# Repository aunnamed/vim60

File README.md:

## Vim60 Mechanical Keyboard

> Description
>
> * A 60% layout mechanical keyboard.
>
>

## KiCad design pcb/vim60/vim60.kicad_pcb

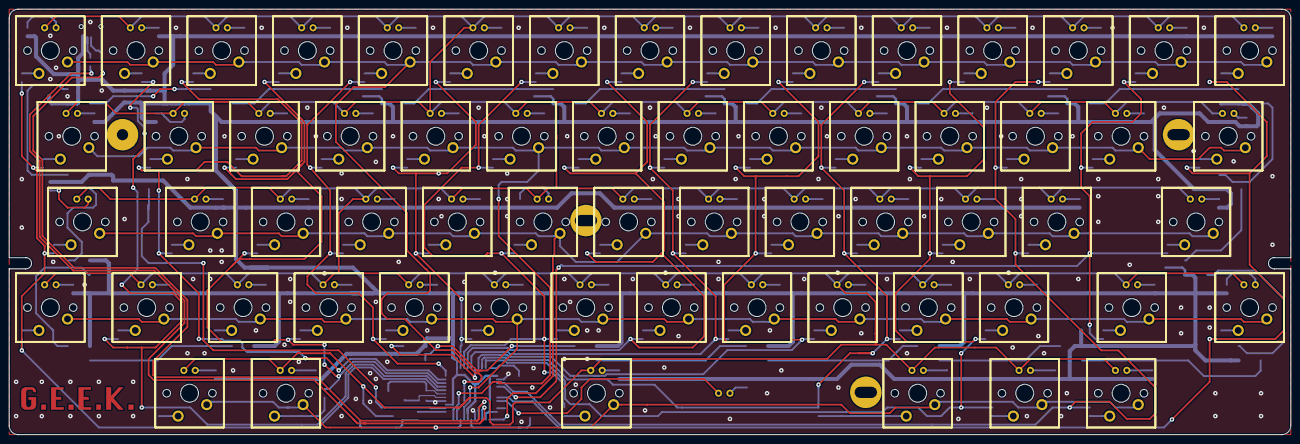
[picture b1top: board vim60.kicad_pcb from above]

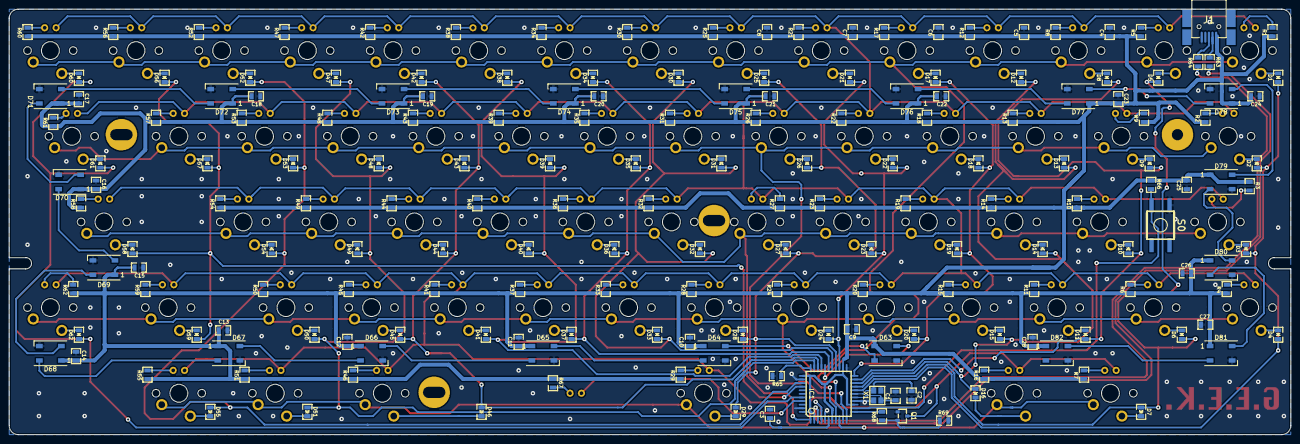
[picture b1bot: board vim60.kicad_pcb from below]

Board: 2 copper layers, 285.0 x 94.6 mm, 313 parts (184 on the bottom side), 180 nets.

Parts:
C1, C2: 22p; 0805C
C3, C4: 1u; 0805C
C5, C6, C7, C8: 100n; 0805C
C9, C10, C11, C12, C13, C14, C15, C16, C17, C18, C19, C20, C21, C22, C23, C24, C25, C26, C27, C28: 100nf; 0805C
D1, D2, D3, D4, D5, D6, D7, D8, D9, D10, D11, D12, D13, D14, D15, D16, D17, D18, D19, D20, D21, D22, D23, D24, D25, D26, D27, D28, D29, D30, D31, D32, D33, D34, D35, D36, D37, D38, D39, D40, D41, D42, D43, D44, D45, D46, D47, D48, D49, D50, D51, D52, D53, D54, D55, D56, D57, D58, D59, D60, D61, D62: 1N4148; 0805D
D63, D64, D65, D66, D67, D68, D69, D70, D71, D72, D73, D74, D75, D76, D77, D78, D79, D80, D81, D82: WS2812B; LED_WS2812B_PLCC4_5.0x5.0mm_P3.2mm
DB1, DB2, DB3, DB4, DB5, DB6, DB7, DB8, DB9, DB10, DB11, DB12, DB13, DB14, DB15, DB16, DB17, DB18, DB19, DB20, DB21, DB22, DB23, DB24, DB25, DB26, DB27, DB28, DB29, DB30, DB31, DB32, DB33, DB34, DB35, DB36, DB37, DB38, DB39, DB40, DB41, DB42, DB43, DB44, DB45, DB46, DB47, DB48, DB49, DB50, DB51, DB52, DB53, DB54, DB55, DB56, DB57, DB58, DB59, DB60, DB61, DB62: LED; MX1A-led
DB63: LED; caps_led
HOLE: VAL**; PKRH
HOLE#2, HOLE#3: VAL**; PKRH
HOLE#4: VAL**; PKRHC
IC1: ATMEGA32U4; TQFP44
J1: USBMINI_B05; 67503
Q1: NPN; 2SC5866
R1, R2, R3, R4, R5, R6, R7, R8, R9, R10, R11, R12, R13, R14, R15, R16, R17, R18, R19, R20, R21, R22, R23, R24, R25, R26, R27, R28, R29, R30, R31, R32, R33, R34, R35, R36, R37, R38, R39, R40, R41, R42, R43, R44, R45, R46, R47, R48, R49, R50, R51, R52, R53, R54, R55, R56, R57, R58, R59, R60, R61, R62: 250; 0805R
R63, R64: 22; 0805R
R65, R66: 10k; 0805R
R67: 300; 0805R
R68, R69: R; 0805R
S0: DTSM-6; KSEM31GLFS
S1, S2, S3, S4, S5, S6, S7, S8, S9, S10, S11, S12, S13, S14, S15, S16, S17, S18, S19, S20, S21, S22, S23, S24, S25, S26, S27, S28, S29, S30, S31, S32, S33, S34, S35, S36, S37, S38, S39, S40, S41, S42, S43, S44, S45, S46, S47, S48, S49, S50, S51, S52, S53, S54, S55, S56, S57, S58, S59, S60, S61, S62: MX1A
X1: ASX4; 4-SMD

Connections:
/CAPS_LED: DB63.2, IC1.41
/bl: IC1.12, R68.2
/col01: D1.1, D2.1, D3.1, D4.1, IC1.18
/col02: D5.1, D6.1, D7.1, IC1.19
/col03: D8.1, D9.1, D10.1, D11.1, IC1.21
/col04: D12.1, D13.1, D14.1, D15.1, D16.1, IC1.20
/col05: D17.1, D18.1, D19.1, D20.1, IC1.22
/col06: D21.1, D22.1, D23.1, D24.1, IC1.25
/col07: D25.1, D26.1, D27.1, D28.1, D29.1, IC1.26
/col08: D30.1, D31.1, D32.1, D33.1, IC1.27
/col09: D34.1, D35.1, D36.1, D37.1, IC1.28
/col10: D38.1, D39.1, D40.1, D41.1, IC1.30
/col11: D42.1, D43.1, D44.1, D45.1, D46.1, IC1.31
/col12: D47.1, D48.1, D49.1, D50.1, D51.1, IC1.32
/col13: D52.1, D53.1, D54.1, D55.1, IC1.36
/col14: D56.1, D57.1, D58.1, D59.1, IC1.37
/col15: D60.1, D61.1, D62.1, IC1.40
/rgb: D63.4, IC1.29
/row01: IC1.10, S1.1, S5.1, S8.1, S12.1, S17.1, S21.1, S25.1, S30.1, S34.1, S38.1, S42.1, S47.1, S52.1, S56.1, S60.1
/row02: IC1.11, S2.1, S9.1, S13.1, S18.1, S22.1, S26.1, S31.1, S35.1, S39.1, S43.1, S48.1, S53.1, S57.1, S61.1
/row03: IC1.1, S3.1, S10.1, S14.1, S19.1, S23.1, S27.1, S32.1, S36.1, S40.1, S44.1, S49.1, S54.1, S58.1
/row04: IC1.8, S4.1, S6.1, S11.1, S15.1, S20.1, S24.1, S28.1, S33.1, S37.1, S41.1, S45.1, S50.1, S59.1, S62.1
/row05: IC1.9, S7.1, S16.1, S29.1, S46.1, S51.1, S55.1
GND: C1.2, C2.2, C3.2, C4.2, C5.2, C6.2, C7.2, C8.2, C9.1, C10.1, C11.1, C12.1, C13.1, C14.1, C15.1, C16.1, C17.1, C18.1, C19.1, C20.1, C21.1, C22.1, C23.1, C24.1, C25.1, C26.1, C27.1, C28.1, D63.3, D64.3, D65.3, D66.3, D67.3, D68.3, D69.3, D70.3, D71.3, D72.3, D73.3, D74.3, D75.3, D76.3, D77.3, D78.3, D79.3, D80.3, D81.3, D82.3, IC1.5, IC1.15, IC1.23, IC1.35, IC1.43, J1.5, Q1.1, R65.2, R69.2, S0.1, X1.2, X1.4
unnamed: C1.1, IC1.16, X1.1
unnamed: C2.1, IC1.17, X1.3
unnamed: C3.1, IC1.6
unnamed: D1.2, S1.2
unnamed: D2.2, S2.2
unnamed: D3.2, S3.2
unnamed: D4.2, S4.2
unnamed: D5.2, S5.2
unnamed: D6.2, S6.2
unnamed: D7.2, S7.2
unnamed: D8.2, S8.2
unnamed: D9.2, S9.2
unnamed: D10.2, S10.2
unnamed: D11.2, S11.2
unnamed: D12.2, S12.2
unnamed: D13.2, S13.2
unnamed: D14.2, S14.2
unnamed: D15.2, S15.2
unnamed: D16.2, S16.2
unnamed: D17.2, S17.2
unnamed: D18.2, S18.2
unnamed: D19.2, S19.2
unnamed: D20.2, S20.2
unnamed: D21.2, S21.2
unnamed: D22.2, S22.2
unnamed: D23.2, S23.2
unnamed: D24.2, S24.2
unnamed: D25.2, S25.2
unnamed: D26.2, S26.2
unnamed: D27.2, S27.2
unnamed: D28.2, S28.2
unnamed: D29.2, S29.2
unnamed: D30.2, S30.2
unnamed: D31.2, S31.2
unnamed: D32.2, S32.2
unnamed: D33.2, S33.2
unnamed: D34.2, S34.2
unnamed: D35.2, S35.2
unnamed: D36.2, S36.2
unnamed: D37.2, S37.2
unnamed: D38.2, S38.2
unnamed: D39.2, S39.2
unnamed: D40.2, S40.2
unnamed: D41.2, S41.2
unnamed: D42.2, S42.2
unnamed: D43.2, S43.2
unnamed: D44.2, S44.2
unnamed: D45.2, S45.2
unnamed: D46.2, S46.2
unnamed: D47.2, S47.2
unnamed: D48.2, S48.2
unnamed: D49.2, S49.2
unnamed: D50.2, S50.2
unnamed: D51.2, S51.2
unnamed: D52.2, S52.2
unnamed: D53.2, S53.2
unnamed: D54.2, S54.2
unnamed: D55.2, S55.2
unnamed: D56.2, S56.2
unnamed: D57.2, S57.2
unnamed: D58.2, S58.2
unnamed: D59.2, S59.2
unnamed: D60.2, S60.2
unnamed: D61.2, S61.2
unnamed: D62.2, S62.2
unnamed: D63.2, D64.4
unnamed: D64.2, D65.4
unnamed: D65.2, D66.4
unnamed: D66.2, D67.4
unnamed: D67.2, D68.4
unnamed: D68.2, D69.4
unnamed: D69.2, D70.4
unnamed: D70.2, D71.4
unnamed: D71.2, D72.4
unnamed: D72.2, D73.4
unnamed: D73.2, D74.4
unnamed: D74.2, D75.4
unnamed: D75.2, D76.4
unnamed: D76.2, D77.4
unnamed: D77.2, D78.4
unnamed: D78.2, D79.4
unnamed: D79.2, D80.4
unnamed: D80.2, D81.4
unnamed: D81.2, D82.4
unnamed: DB1.1, R1.2
unnamed: DB1.2, DB2.2, DB3.2, DB4.2, DB5.2, DB6.2, DB7.2, DB8.2, DB9.2, DB10.2, DB11.2, DB12.2, DB13.2, DB14.2, DB15.2, DB16.2, DB17.2, DB18.2, DB19.2, DB20.2, DB21.2, DB22.2, DB23.2, DB24.2, DB25.2, DB26.2, DB27.2, DB28.2, DB29.2, DB30.2, DB31.2, DB32.2, DB33.2, DB34.2, DB35.2, DB36.2, DB37.2, DB38.2, DB39.2, DB40.2, DB41.2, DB42.2, DB43.2, DB44.2, DB45.2, DB46.2, DB47.2, DB48.2, DB49.2, DB50.2, DB51.2, DB52.2, DB53.2, DB54.2, DB55.2, DB56.2, DB57.2, DB58.2, DB59.2, DB60.2, DB61.2, DB62.2, Q1.3
unnamed: DB2.1, R2.2
unnamed: DB3.1, R3.2
unnamed: DB4.1, R4.2
unnamed: DB5.1, R5.2
unnamed: DB6.1, R6.2
unnamed: DB7.1, R7.2
unnamed: DB8.1, R8.2
unnamed: DB9.1, R9.2
unnamed: DB10.1, R10.2
unnamed: DB11.1, R11.2
unnamed: DB12.1, R12.2
unnamed: DB13.1, R13.2
unnamed: DB14.1, R14.2
unnamed: DB15.1, R15.2
unnamed: DB16.1, R16.2
unnamed: DB17.1, R17.2
unnamed: DB18.1, R18.2
unnamed: DB19.1, R19.2
unnamed: DB20.1, R20.2
unnamed: DB21.1, R21.2
unnamed: DB22.1, R22.2
unnamed: DB23.1, R23.2
unnamed: DB24.1, R24.2
unnamed: DB25.1, R25.2
unnamed: DB26.1, R26.2
unnamed: DB27.1, R27.2
unnamed: DB28.1, R28.2
unnamed: DB29.1, R29.2
unnamed: DB30.1, R30.2
unnamed: DB31.1, R31.2
unnamed: DB32.1, R32.2
unnamed: DB33.1, R33.2
unnamed: DB34.1, R34.2
unnamed: DB35.1, R35.2
unnamed: DB36.1, R36.2
unnamed: DB37.1, R37.2
unnamed: DB38.1, R38.2
unnamed: DB39.1, R39.2
unnamed: DB40.1, R40.2
unnamed: DB41.1, R41.2
unnamed: DB42.1, R42.2
unnamed: DB43.1, R43.2
unnamed: DB44.1, R44.2
unnamed: DB45.1, R45.2
unnamed: DB46.1, R46.2
unnamed: DB47.1, R47.2
unnamed: DB48.1, R48.2
unnamed: DB49.1, R49.2
unnamed: DB50.1, R50.2
unnamed: DB51.1, R51.2
unnamed: DB52.1, R52.2
unnamed: DB53.1, R53.2
unnamed: DB54.1, R54.2
unnamed: DB55.1, R55.2
unnamed: DB56.1, R56.2
unnamed: DB57.1, R57.2
unnamed: DB58.1, R58.2
unnamed: DB59.1, R59.2
unnamed: DB60.1, R60.2
unnamed: DB61.1, R61.2
unnamed: DB62.1, R62.2
unnamed: DB63.1, R67.2
unnamed: IC1.3, R63.1
unnamed: IC1.4, R64.1
unnamed: IC1.13, R66.2, S0.3
unnamed: IC1.33, R65.1
unnamed: J1.2, R63.2
unnamed: J1.3, R64.2
unnamed: Q1.2, R68.1, R69.1
VCC: C4.1, C5.1, C6.1, C7.1, C8.1, C9.2, C10.2, C11.2, C12.2, C13.2, C14.2, C15.2, C16.2, C17.2, C18.2, C19.2, C20.2, C21.2, C22.2, C23.2, C24.2, C25.2, C26.2, C27.2, C28.2, D63.1, D64.1, D65.1, D66.1, D67.1, D68.1, D69.1, D70.1, D71.1, D72.1, D73.1, D74.1, D75.1, D76.1, D77.1, D78.1, D79.1, D80.1, D81.1, D82.1, IC1.2, IC1.7, IC1.14, IC1.24, IC1.34, IC1.44, J1.1, R1.1, R2.1, R3.1, R4.1, R5.1, R6.1, R7.1, R8.1, R9.1, R10.1, R11.1, R12.1, R13.1, R14.1, R15.1, R16.1, R17.1, R18.1, R19.1, R20.1, R21.1, R22.1, R23.1, R24.1, R25.1, R26.1, R27.1, R28.1, R29.1, R30.1, R31.1, R32.1, R33.1, R34.1, R35.1, R36.1, R37.1, R38.1, R39.1, R40.1, R41.1, R42.1, R43.1, R44.1, R45.1, R46.1, R47.1, R48.1, R49.1, R50.1, R51.1, R52.1, R53.1, R54.1, R55.1, R56.1, R57.1, R58.1, R59.1, R60.1, R61.1, R62.1, R66.1, R67.1

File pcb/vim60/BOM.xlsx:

XXXX 项目物料BOM清单
序号 | 名称 | 型号/规格 | 封装 | 用量 | 品牌 | 商品编号
示例：
1 | 电源芯片 | AMS1117-3.3 | SOT-223 | 1 | AMS | C6186
2 | 贴片电阻 | 10KΩ(1002) ±1% | 0402 | 10 | YAGEO | C93943
3 | 贴片电阻 | 4.7KΩ(4701) ±1% | 0603 | 20 | uniohm | C23162
请删除 第3~7行 示例部分内容！
1 | NPN三极管 | 2SC5866 | SOT-346T | 1 | ROHM | C126305
2 | 贴片电容 | 22pf | 0805C | 2
3 | 贴片电容 | 1u | 0805C | 2
4 | 贴片电容 | 100n | 0805C | 24
5 | 二极管 | 1N4148 | 0805D | 62
6 | LED | WS2812B |  | 20
7 | IC | ATMEGA32U4 | TQFP44 | 1
8 | USB连接器 | 67503
9 | 贴片电阻 |  | 0805R | 2
10 | 贴片电阻 | 250ohm | 0805R | 62
11 | 贴片电阻 | 22ohm | 0805R | 2
12 | 贴片电阻 | 10k | 0805R | 2
13 | 贴片电阻 | 300ohm | 0805R | 1
14 | 轻触开关 | KSEM31GLFS |  | 1 | DTSM-6
15 | 晶振 | ASX4 | 4-SMD | 1
请将需要匹配的BOM放在第一个工作表即sheet1

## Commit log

2020-02-23 layout&plate
2020-03-03 matrix&led
2020-05-17 200517
2020-06-07 making bom
2020-06-07 readme
2020-06-17 finished
2020-07-18 new logo
2021-01-29 mv fn key left
